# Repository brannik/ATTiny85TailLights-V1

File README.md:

# ATTinyTailLights
ATTiny tail lights
Schematic and gerver files

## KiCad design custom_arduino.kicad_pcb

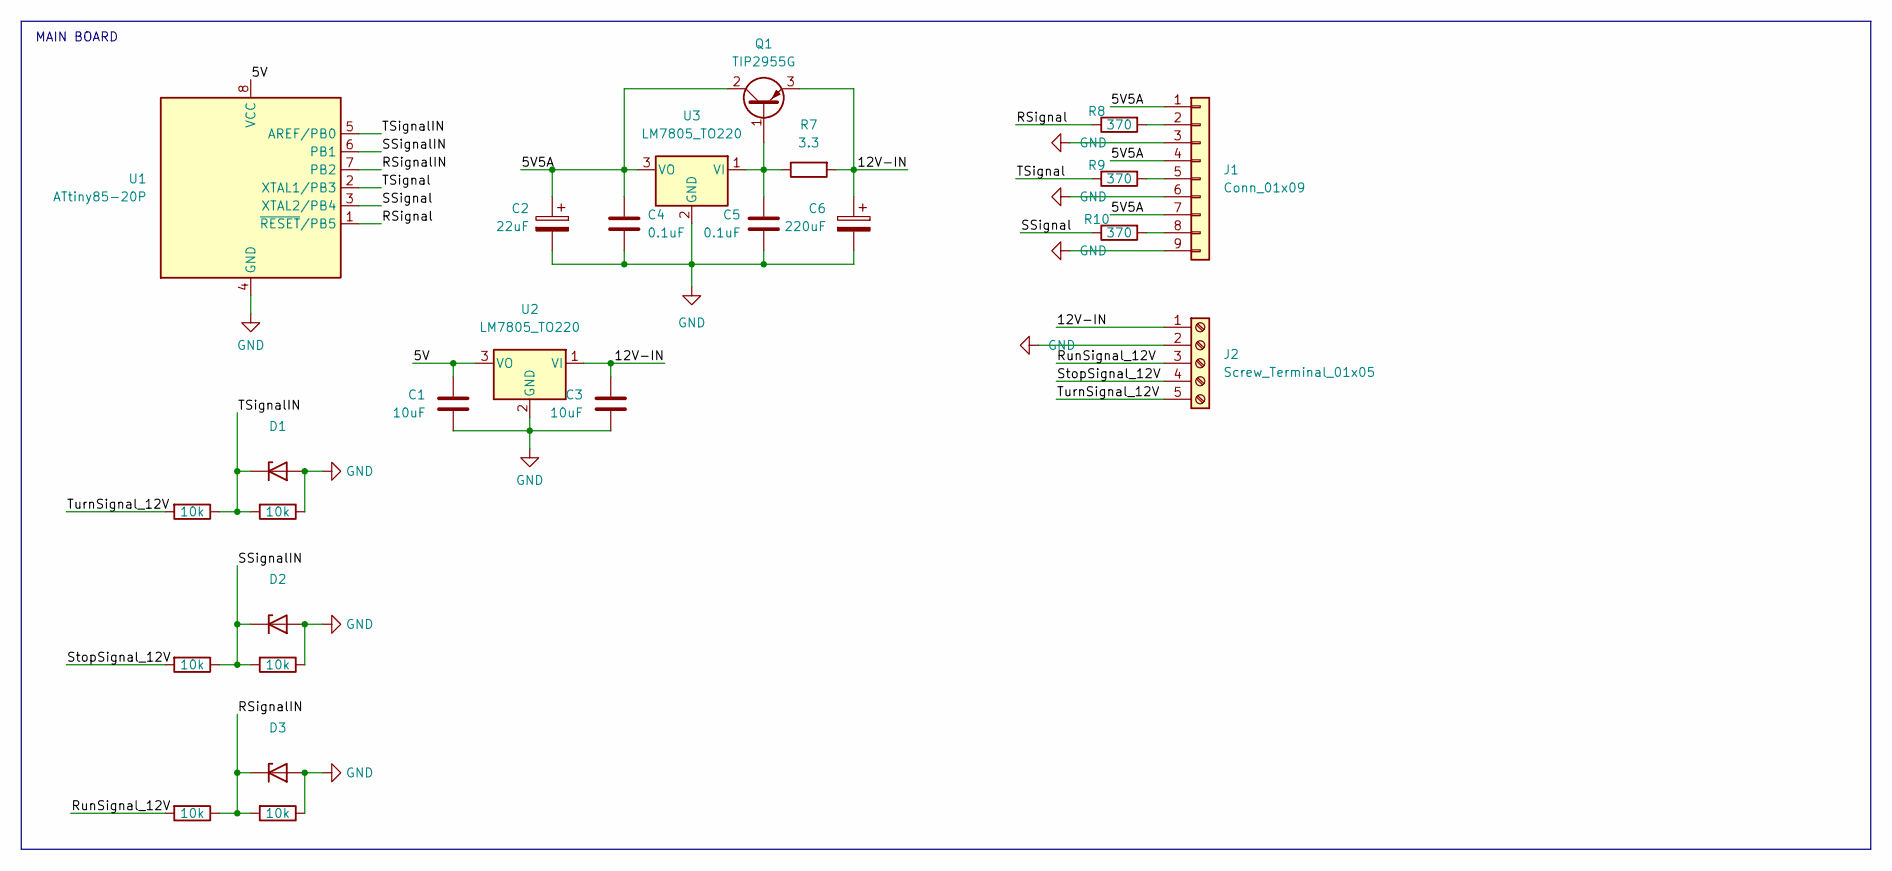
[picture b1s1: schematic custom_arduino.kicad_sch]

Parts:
C1, C3: 10uF; C_Disc_D3.0mm_W2.0mm_P2.50mm
C2: 22uF; CP_Radial_D5.0mm_P2.50mm
C4, C5: 0.1uF; C_Disc_D3.0mm_W2.0mm_P2.50mm
C6: 220uF; CP_Radial_D5.0mm_P2.50mm
D1, D2, D3: 1N47xxA; D_DO-41_SOD81_P3.81mm_Vertical_AnodeUp
J1: Conn_01x09; PinHeader_1x09_P2.54mm_Vertical
J2: Screw_Terminal_01x05; mors_5p
Q1: TIP2955G; TO-247-3_Horizontal_TabUp
R1, R2, R3, R4, R5, R6: 10k; R_Axial_DIN0207_L6.3mm_D2.5mm_P2.54mm_Vertical
R7: 3.3; R_Axial_Power_L20.0mm_W6.4mm_P22.40mm
R8, R9, R10: 370; R_Axial_DIN0207_L6.3mm_D2.5mm_P2.54mm_Vertical
U1: ATtiny85-20P; DIP-8_W7.62mm
U2, U3: LM7805_TO220; TO-220-3_Horizontal_TabDown

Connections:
/5V: C1.1, U1.8 (VCC), U2.3 (VO)
/5V5A: C2.1, C4.1, J1.1, J1.4, J1.7, Q1.2 (C), U3.3 (VO)
/12V-IN: C3.1, C6.1, J2.1, Q1.3 (E), R7.2, U2.1 (VI)
/RSignal: R8.1, U1.1 (~RESET/PB5)
/RSignalIN: D3.1 (K), R3.1, R6.2, U1.7 (PB2)
/RunSignal_12V: J2.3, R3.2
/SSignal: R10.1, U1.3 (XTAL2/PB4)
/SSignalIN: D2.1 (K), R2.1, R5.2, U1.6 (PB1)
/StopSignal_12V: J2.4, R2.2
/TSignal: R9.1, U1.2 (XTAL1/PB3)
/TSignalIN: D1.1 (K), R1.1, R4.2, U1.5 (AREF/PB0)
/TurnSignal_12V: J2.5, R1.2
GND: C1.2, C2.2, C3.2, C4.2, C5.2, C6.2, D1.2 (A), D2.2 (A), D3.2 (A), J1.3, J1.6, J1.9, J2.2, R4.1, R5.1, R6.1, U1.4 (GND), U2.2 (GND), U3.2 (GND)
unnamed: C5.1, Q1.1 (B), R7.1, U3.1 (VI)
unnamed: J1.2, R8.2
unnamed: J1.5, R9.2
unnamed: J1.8, R10.2

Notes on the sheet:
MAIN BOARD

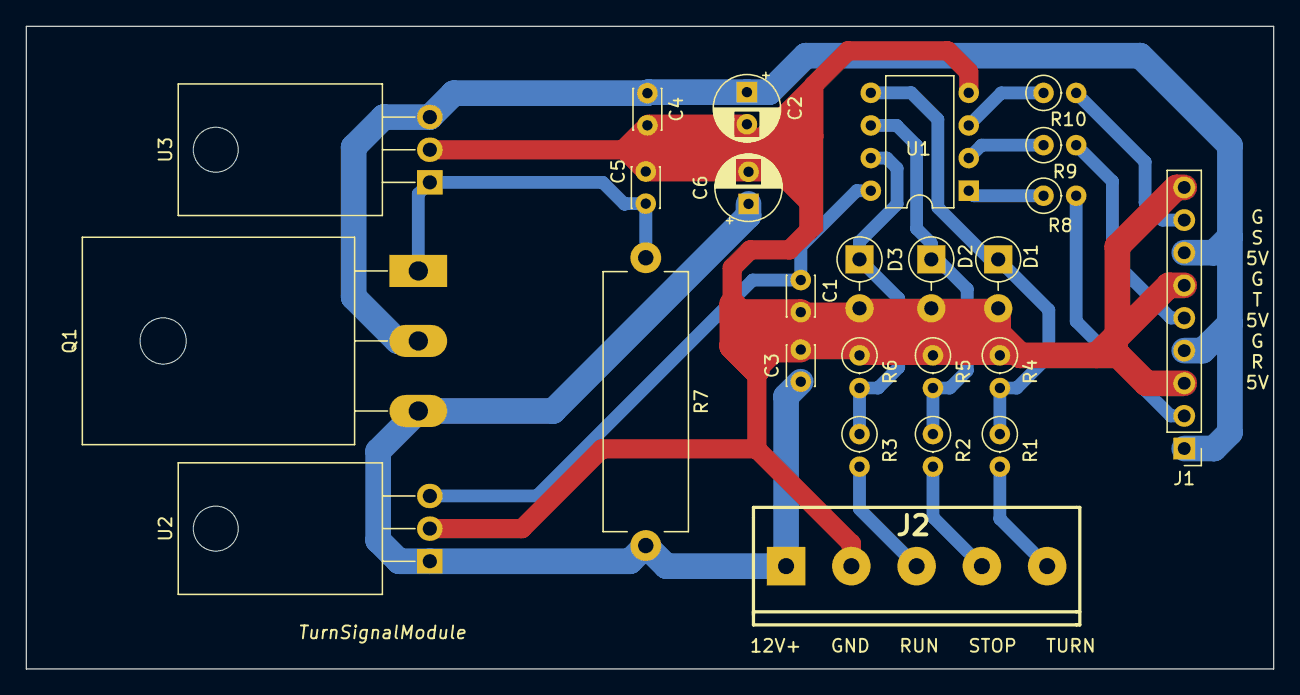
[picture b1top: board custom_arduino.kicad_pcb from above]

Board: 2 copper layers, 97.1 x 50.0 mm, 25 parts (0 on the bottom side), 17 nets.

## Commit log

2023-06-12 initial
